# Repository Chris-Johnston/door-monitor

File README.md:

# door-monitor

An IOT solution to forgetting to lock the door using an ESP32 and a Flask
server. Integrates with Home Assistant and Discord to provide instant
notification of the locked or unlocked state of the door lock and the state
of the door being open.

Using Home Assistant and Twilio, I can text myself when I leave the
house without locking:

## Description

This uses an ESP32 dev board connected to two reed switches, one placed on the
door frame, one on the door lock. Hourly, and when the state of the lock or
door sensors are set to "open",
the board will log to the Flask server that collects this data.

The included magnets to pair with the reed switches I bought were too big
to fit where I needed them, so I used stronger, smaller magnets that
I taped to the lock and the door frame.

The data sent from the ESP32 to the Flask server gets forwarded
along to each of the configured webhooks. This can be configured
using the webserver.

This integrates with Home Assistant very well.

Using the ESP32's "deep sleep" mode and pin interrupts,
the ESP32 is able to run using very little power.

While the ESP32 is very light on power, the dev board that I'm using
is not.
Even with the power LED removed,
the board was measured to run at 9.8mA in deep sleep mode.
Most of the current
draw is from the USB Controller and voltage regulator.

Running on 4 AA batteries in series (2000-3000 mAh),
the sensor is estimated to run for roughly 200-300 hours.
While this is _okay_, it's not great.
In the future I may change to a more "barebones" solution
that does not include this unnecessary power draw.

## Running the Flask Server

The Flask server runs using Docker. The `uwsgi-nginx-flask`
[image must be built manually if running on a Raspberry Pi.](https://github.com/tiangolo/uwsgi-nginx-flask-docker/issues/67)

When debugging, the server can be started using:

```console
./start_docker_debug.sh
```

When deployed, the server can be started using:

```console
./start_docker.sh
```

## Uploading the sensor-client

The sensor-client is built using Arduino. Ensure that the ESP32 board is
installed.
The Arduino extension for VS Code can upload this sketch.

Modify `config.h` with the wifi settings, URL of the server,
and the pins and names of each of the sensors.

```cpp
#define WIFI_SSID "wifi ssid"
#define WIFI_PSK  "psk"

#define REPORTING_URL "http://10.1.1.2/api/sensor"

// define the sensors
Sensor sensors[] = {
    // pin must be one of 0,2,4,12-15,25-27,32-39
    // those support interrupts while in deep sleep
    // { pin, name of sensor }
    { 32, "LOCK" },
    { 33, "DOOR" },
};

#define NUM_SENSORS 2
```

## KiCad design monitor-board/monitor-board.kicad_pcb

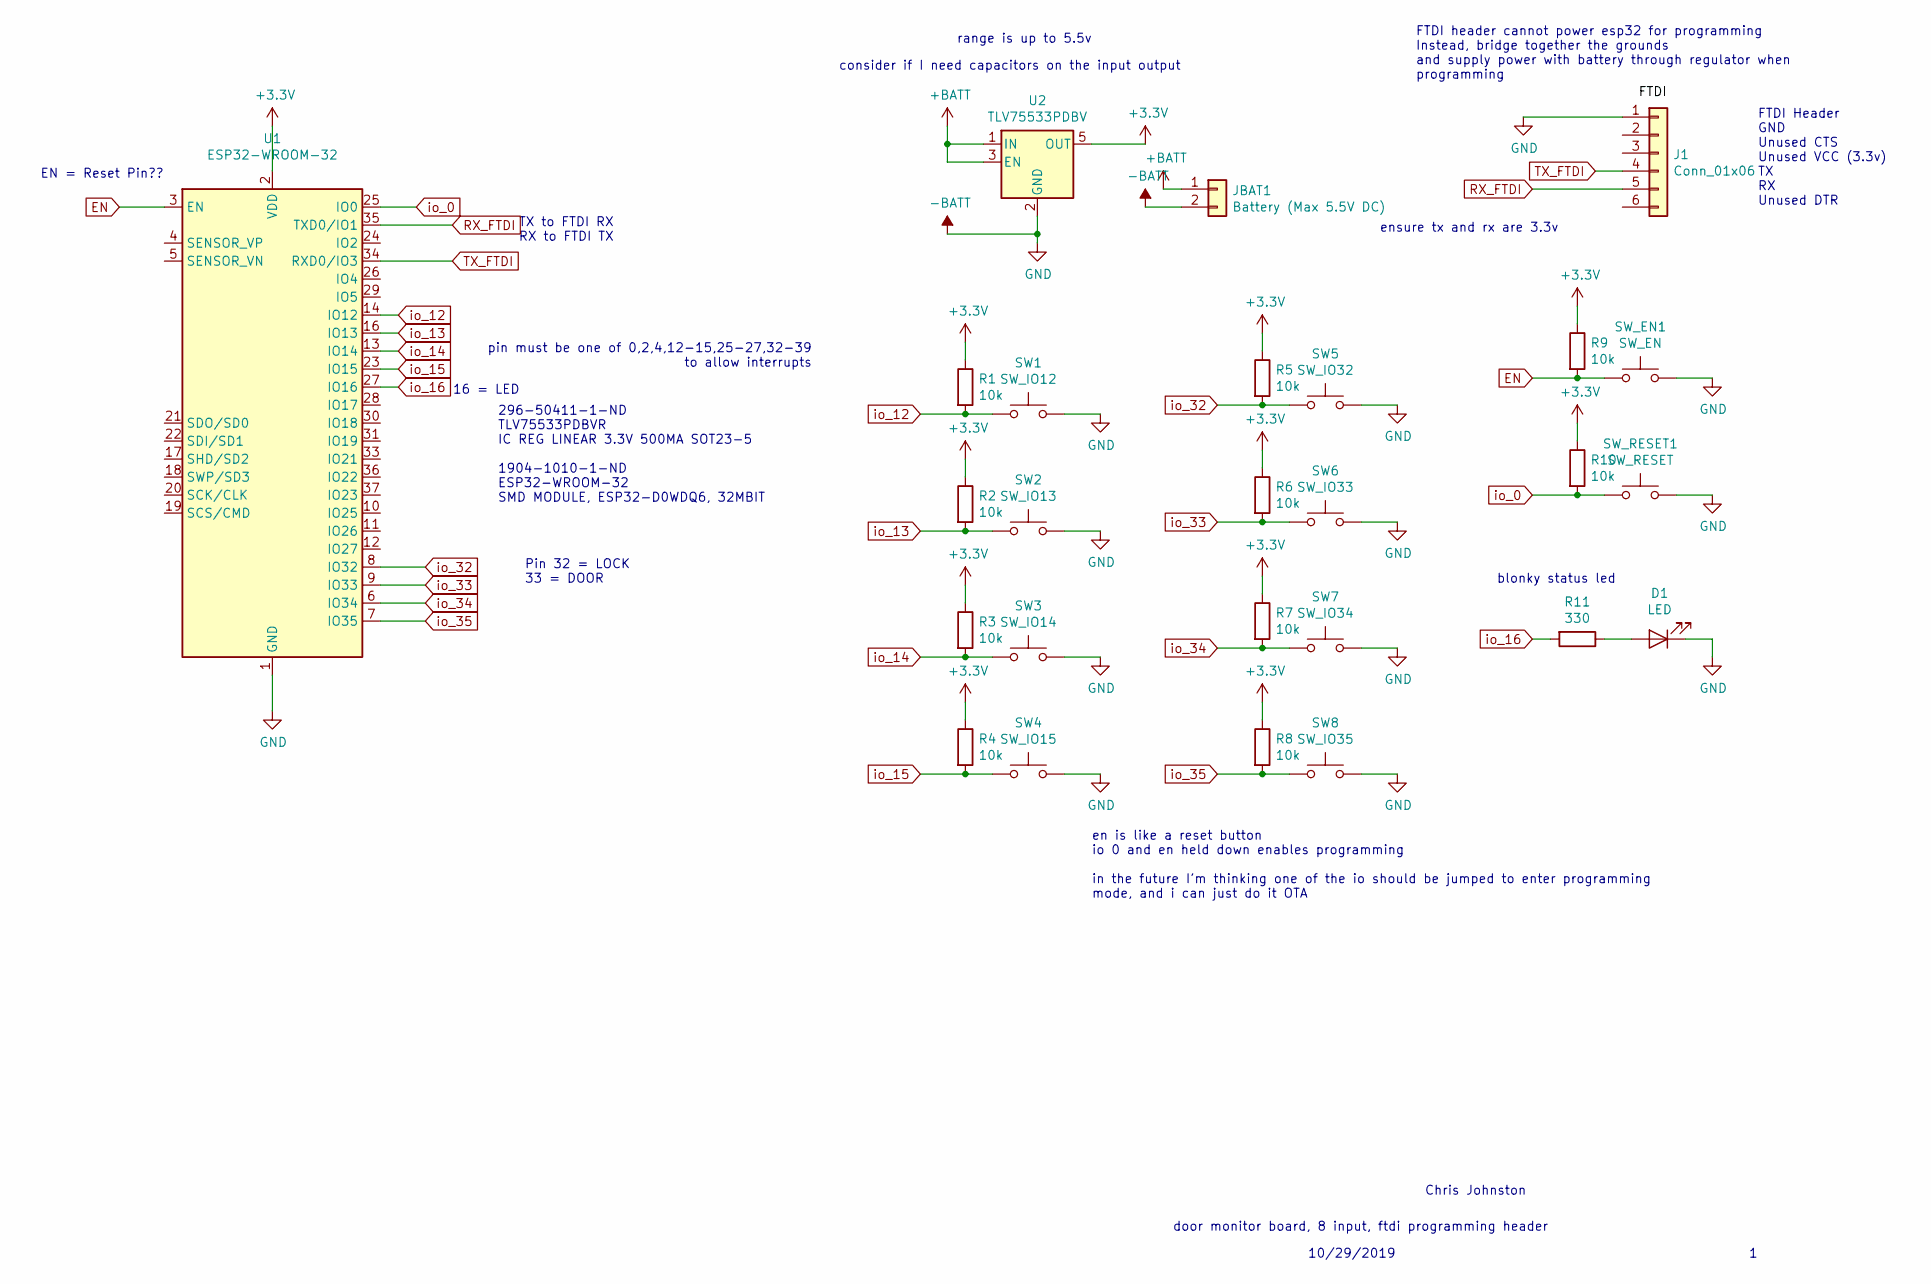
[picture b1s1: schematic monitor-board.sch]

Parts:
D1: LED; LED_0603_1608Metric_Pad1.05x0.95mm_HandSolder
J1: Conn_01x06; PinSocket_1x06_P2.54mm_Vertical
JBAT1: Battery (Max 5.5V DC); TerminalBlock_Phoenix_PT-1,5-2-5.0-H_1x02_P5.00mm_Horizontal
R1, R2, R3, R4, R5, R6, R7, R8, R9, R10: 10k; R_0603_1608Metric_Pad1.05x0.95mm_HandSolder
R11: 330; R_0603_1608Metric_Pad1.05x0.95mm_HandSolder
SW1: SW_IO12; TerminalBlock_Phoenix_PT-1,5-2-5.0-H_1x02_P5.00mm_Horizontal
SW2: SW_IO13; TerminalBlock_Phoenix_PT-1,5-2-5.0-H_1x02_P5.00mm_Horizontal
SW3: SW_IO14; TerminalBlock_Phoenix_PT-1,5-2-5.0-H_1x02_P5.00mm_Horizontal
SW4: SW_IO15; TerminalBlock_Phoenix_PT-1,5-2-5.0-H_1x02_P5.00mm_Horizontal
SW5: SW_IO32; TerminalBlock_Phoenix_PT-1,5-2-5.0-H_1x02_P5.00mm_Horizontal
SW6: SW_IO33; TerminalBlock_Phoenix_PT-1,5-2-5.0-H_1x02_P5.00mm_Horizontal
SW7: SW_IO34; TerminalBlock_Phoenix_PT-1,5-2-5.0-H_1x02_P5.00mm_Horizontal
SW8: SW_IO35; TerminalBlock_Phoenix_PT-1,5-2-5.0-H_1x02_P5.00mm_Horizontal
SW_EN1: SW_EN; SW_PUSH_6mm
SW_RESET1: SW_RESET; SW_PUSH_6mm
U1: ESP32-WROOM-32
U2: TLV75533PDBV; SOT-23-5

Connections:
+3V3: R1.1, R2.1, R3.1, R4.1, R5.1, R6.1, R7.1, R8.1, R9.1, R10.1, U1.2 (VDD), U2.5 (OUT)
+BATT: JBAT1.1, U2.1 (IN), U2.3 (EN)
-BATT: D1.1 (K), J1.1, JBAT1.2, SW1.2, SW2.2, SW3.2, SW4.2, SW5.2, SW6.2, SW7.2, SW8.2, SW_EN1.2, SW_RESET1.2, U1.1 (GND), U1.15 (GND), U1.38 (GND), U1.39 (GND), U2.2 (GND)
EN: R9.2, SW_EN1.1, U1.3 (EN)
unnamed: D1.2 (A), R11.1
RX_FTDI: J1.5, U1.35 (TXD0/IO1)
TX_FTDI: J1.4, U1.34 (RXD0/IO3)
io_0: R10.2, SW_RESET1.1, U1.25 (IO0)
io_12: R1.2, SW1.1, U1.14 (IO12)
io_13: R2.2, SW2.1, U1.16 (IO13)
io_14: R3.2, SW3.1, U1.13 (IO14)
io_15: R4.2, SW4.1, U1.23 (IO15)
io_16: R11.2, U1.27 (IO16)
io_32: R5.2, SW5.1, U1.8 (IO32)
io_33: R6.2, SW6.1, U1.9 (IO33)
io_34: R7.2, SW7.1, U1.6 (IO34)
io_35: R8.2, SW8.1, U1.7 (IO35)

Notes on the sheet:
FTDI Header GND Unused CTS Unused VCC (3.3v) TX RX Unused DTR
TX to FTDI RX RX to FTDI TX
EN = Reset Pin??
pin must be one of 0,2,4,12-15,25-27,32-39 to allow interrupts
296-50411-1-ND‎ ‎TLV75533PDBVR‎ IC REG LINEAR 3.3V 500MA SOT23-5 1904-1010-1-ND‎ ‎ESP32-WROOM-32‎ SMD MODULE, ESP32-D0WDQ6, 32MBIT
Pin 32 = LOCK 33 = DOOR
consider if I need capacitors on the input output
en is like a reset button io 0 and en held down enables programming in the future I'm thinking one of the io should be jumped to enter programming mode, and i can just do it OTA
blonky status led
door monitor board, 8 input, ftdi programming header
10/29/2019
Chris Johnston
16 = LED
ensure tx and rx are 3.3v
FTDI header cannot power esp32 for programming Instead, bridge together the grounds and supply power with battery through regulator when programming
range is up to 5.5v

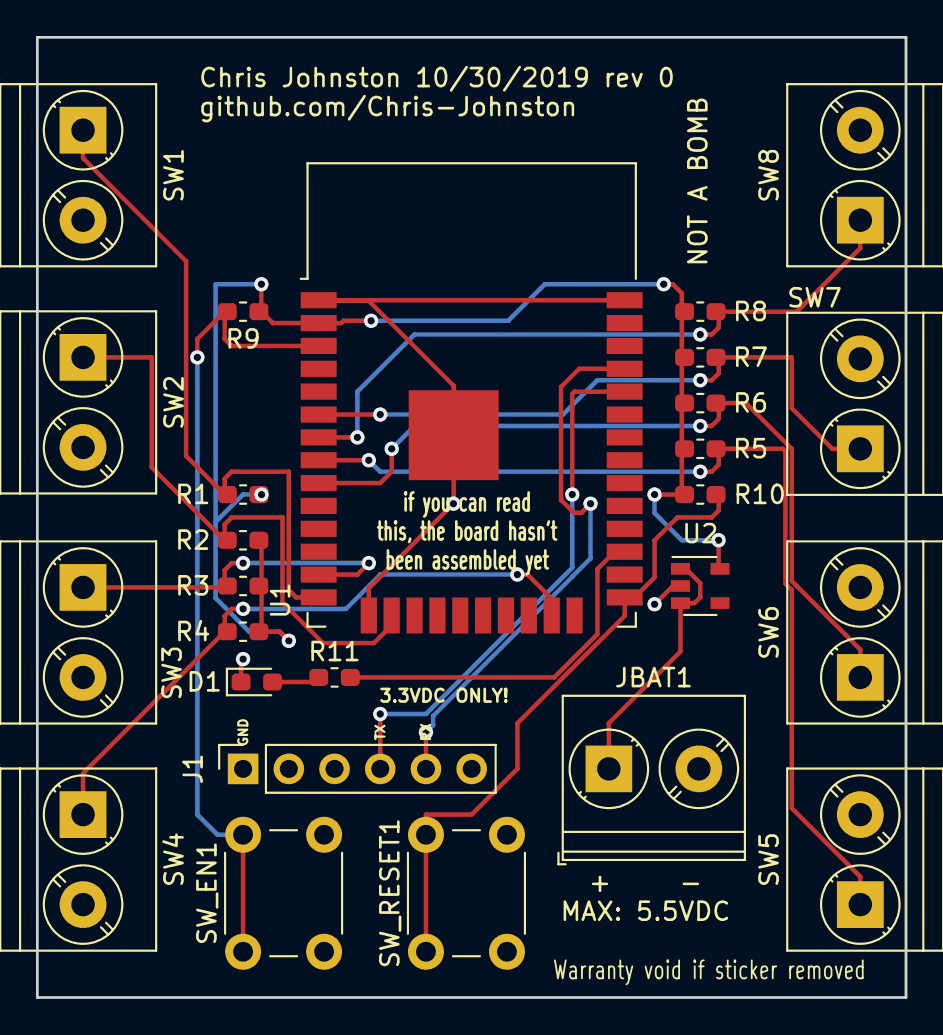
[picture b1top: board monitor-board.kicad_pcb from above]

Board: 2 copper layers, 48.3 x 53.3 mm, 26 parts (0 on the bottom side), 17 nets.

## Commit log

2019-10-10 wip version of flask app
2019-10-10 add very wip version of sensor client
2019-10-10 cleanup the client code
2019-10-10 add TODO
2019-10-10 test the root endpoint
2019-10-12 shorten sensor open timer to 5s
2019-10-12 set up database api operations
2019-10-12 remove debug
2019-10-12 report when sensors go low after they are high
2019-10-12 update history endpoints
2019-10-13 fix timestamp field of db
2019-10-13 wip landing page
2019-10-13 wip frontend using d3 timeline
2019-10-15 remove graph stuff that wasn't working
2019-10-17 add webhook functionality and set up settings pages
2019-10-18 ugly, but save and view changes work now
2019-10-20 change path of database
2019-10-20 update docker stuff
2019-10-20 fix persistence of database
2019-10-20 Add script for running the app for debugging
2019-10-20 remove conflicting flags from debug script
2019-10-20 Update README and add pictures
2019-10-20 Use img tags in readme for smaller images
2019-10-20 update readme with minor addition
2019-10-20 Add note about home assistant
2019-10-20 Add example of sms notification
2019-10-22 Add a shorter deep sleep interval for when sensors high
    Adds a shorter deep sleep interval for when sensors are high and stay low for more than 10
    seconds. After 5 minutes, will check the state of the pins once again
2019-10-25 inital commit of monitor-board files
2019-10-25 note down parts that I'm using
2019-10-30 finish first version of monitor board schematic
2019-10-30 setup footprints
2019-10-30 initial layout of footprints
2019-10-30 fix footprints of led and switches
2019-10-30 add traces
2019-10-30 finish routing the PCB
2019-10-30 leave a TODO
2019-10-31 remove todo text, part matched footprint
2019-10-31 Update footprints of resistors and led to go with cheap parts
2019-10-31 dont add crob image
2019-10-31 update silkscreen
2019-10-31 update from refill
2019-10-31 trim edges of board
2019-11-04 Rework the way that pin status is reported while not in deep sleep
2019-11-04 update issue with watchdog timeout in handler
2019-11-04 update poll timer to 6 hours
2019-11-05 additional improvements to inerrupt method
2019-11-05 attempt to fix concurrency issues with sqlite db
2019-11-05 Don't notify discord on interrupt update
2019-11-06 fix #1 add exponential backoff for when pins are open
